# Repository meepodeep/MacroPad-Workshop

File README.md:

# MacroPad-Workshop
macro pad design for the CFMG workshop
# ASSEMBLY STEPS

1. bend the legs of the diodes and put them into the holes labeled d(x) on the back of the pcb (the side with the logo). make sure the black stripe on the diode is pointing to the square hole
2. solder them in from the side where they are sticking out
3. cut the legs off the diodes
4. click the switches into the plate with the pins facing up
5. solder the pin headers that were included with the microcontroller on the back side of the board (side with logo), the short side of the headers go through the pcb.
6. click the switches and plate onto the board and then solder the switches.
7. solder the microcontroller onto the pin headers one pin above the bottom, this is due to an error in the library i used.

# FLASHING STEPS

1. install qmk toolbox
2. install the cmfg_macropad_default.hex file from this repo
3. select it in qmk toolbox
4. select auto flash
5. connect the macropad to your computer and then short the reset and ground pins using some metal thing

# BOM

|Item        |Price|Quantity|Use              |Link                                                                                                                                                                                                                                                                                                                                                                                                                                                                                                                                                                                                                                                                                                                                                  |
|------------|-----|--------|-----------------|------------------------------------------------------------------------------------------------------------------------------------------------------------------------------------------------------------------------------------------------------------------------------------------------------------------------------------------------------------------------------------------------------------------------------------------------------------------------------------------------------------------------------------------------------------------------------------------------------------------------------------------------------------------------------------------------------------------------------------------------------|
|Switches    |5.81 |30pcs   |switches         |https://www.aliexpress.us/item/3256811859979458.html?spm=a2g0o.productlist.main.13.4eea570flhbmL7&algo_pvid=e65426b4-60f4-4fc9-9348-af8a4b587c54&algo_exp_id=e65426b4-60f4-4fc9-9348-af8a4b587c54-12&pdp_ext_f=%7B%22order%22%3A%2220%22%2C%22eval%22%3A%221%22%2C%22fromPage%22%3A%22search%22%7D&pdp_npi=6%40dis%21USD%2112.27%215.77%21%21%2182.80%2138.92%21%40210318a717799006729027642ea09d%2112000057360279622%21sea%21US%214381910819%21X%211%210%21n_tag%3A-29919%3Bd%3A747bdf24%3Bm03_new_user%3A-29895&curPageLogUid=bT9cObGFOkPD&utparam-url=scene%3Asearch%7Cquery_from%3A%7Cx_object_id%3A1005012046294210%7C_p_origin_prod%3A                                                                                                          |
|Pro micro   |4.38 |1       |runs the macropad|https://www.aliexpress.us/item/2251801390587459.html?spm=a2g0o.productlist.main.3.48bf6cd9PQeXzG&algo_pvid=fa6176a7-c4be-416b-9716-300483b20f90&algo_exp_id=fa6176a7-c4be-416b-9716-300483b20f90-2&pdp_ext_f=%7B%22order%22%3A%225295%22%2C%22eval%22%3A%221%22%2C%22fromPage%22%3A%22search%22%7D&pdp_npi=6%40dis%21USD%214.31%214.31%21%21%214.31%214.31%21%402101e2b217799006250502727eef1b%2112000030837890690%21sea%21US%214381910819%21X%211%210%21n_tag%3A-29919%3Bd%3A747bdf24%3Bm03_new_user%3A-29895&curPageLogUid=kLt6ooCUgbaQ&utparam-url=scene%3Asearch%7Cquery_from%3A%7Cx_object_id%3A1576902211%7C_p_origin_prod%3A                                                                                                                   |
|1N4148 Diode|2.68 |1       |is diode         |https://www.aliexpress.us/item/3256804886900665.html?spm=a2g0o.productlist.main.8.31e1648dN5UmVI&aem_p4p_detail=202605270952121212322309854570000188418&algo_pvid=a378f521-9b65-44cc-8d89-a025a8239f06&algo_exp_id=a378f521-9b65-44cc-8d89-a025a8239f06-7&pdp_ext_f=%7B%22order%22%3A%2290%22%2C%22eval%22%3A%221%22%2C%22fromPage%22%3A%22search%22%7D&pdp_npi=6%40dis%21USD%212.68%212.68%21%21%212.68%212.68%21%40210328d417799007320938248e1cda%2112000031530566687%21sea%21US%214381910819%21X%211%210%21n_tag%3A-29919%3Bd%3A747bdf24%3Bm03_new_user%3A-29895&curPageLogUid=XsiQyzmtc2jb&utparam-url=scene%3Asearch%7Cquery_from%3A%7Cx_object_id%3A1005005073215417%7C_p_origin_prod%3A&search_p4p_id=202605270952121212322309854570000188418_2|
|Keycaps     |4.07 |1       |is keycap        |https://www.aliexpress.us/item/3256808845306164.html?spm=a2g0o.productlist.main.3.5b1b5170kbpBCq&algo_pvid=a0e70af7-736c-44be-90c3-9ff2f53e2aa7&algo_exp_id=a0e70af7-736c-44be-90c3-9ff2f53e2aa7-2&pdp_ext_f=%7B%22order%22%3A%22173%22%2C%22eval%22%3A%221%22%2C%22fromPage%22%3A%22search%22%7D&pdp_npi=6%40dis%21USD%214.07%214.07%21%21%214.07%214.07%21%402101e80f17799008263841887effb5%2112000047649050621%21sea%21US%214381910819%21X%211%210%21n_tag%3A-29919%3Bd%3A747bdf24%3Bm03_new_user%3A-29895&curPageLogUid=K3evXPx26JyJ&utparam-url=scene%3Asearch%7Cquery_from%3A%7Cx_object_id%3A1005009031620916%7C_p_origin_prod%3A                                                                                                              |

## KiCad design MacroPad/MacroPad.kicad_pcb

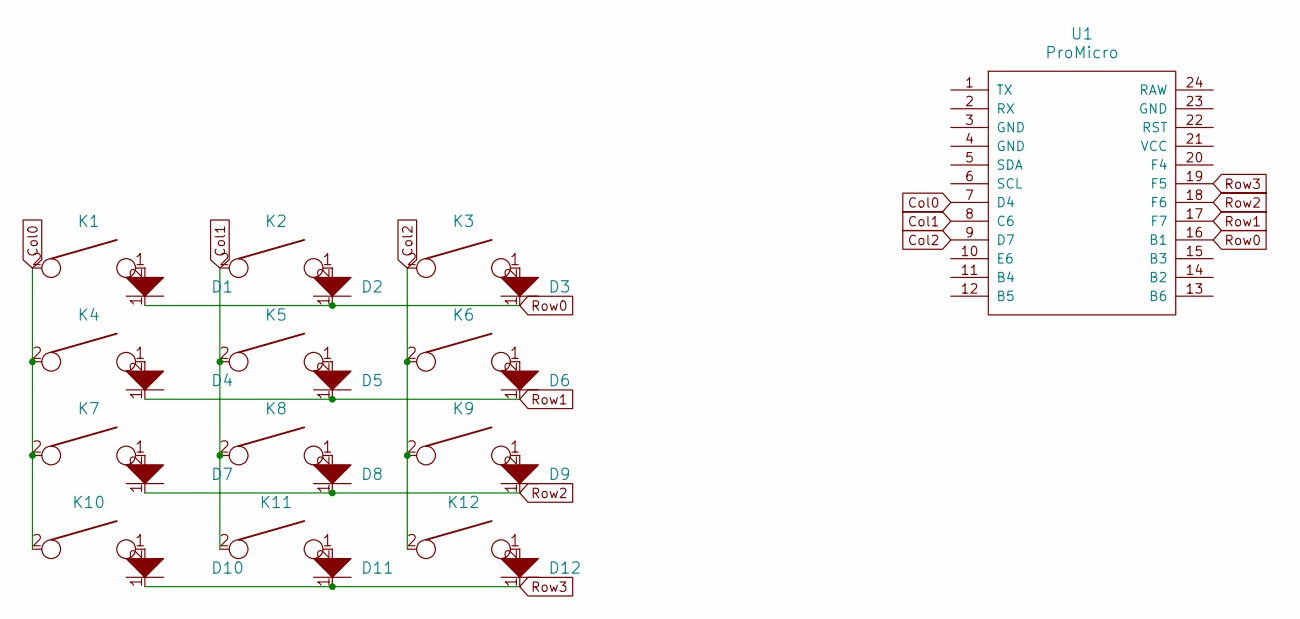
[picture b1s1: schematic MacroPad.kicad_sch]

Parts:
D1, D2, D3, D4, D5, D6, D7, D8, D9, D10, D11, D12: D; D_SOD123_axial
K1, K2, K3, K4, K5, K6, K7, K8, K9, K10, K11, K12: KEYSW; Mx_Alps_100
U1: ProMicro; Pro_Micro

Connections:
Col0: K1.2, K4.2, K7.2, K10.2, U1.7 (D4)
Col1: K2.2, K5.2, K8.2, K11.2, U1.8 (C6)
Col2: K3.2, K6.2, K9.2, K12.2, U1.9 (D7)
unnamed: D1.2, K1.1
unnamed: D2.2, K2.1
unnamed: D3.2, K3.1
unnamed: D4.2, K4.1
unnamed: D5.2, K5.1
unnamed: D6.2, K6.1
unnamed: D7.2, K7.1
unnamed: D8.2, K8.1
unnamed: D9.2, K9.1
unnamed: D10.2, K10.1
unnamed: D11.2, K11.1
unnamed: D12.2, K12.1
Row0: D1.1, D2.1, D3.1, U1.16 (B1)
Row1: D4.1, D5.1, D6.1, U1.17 (F7)
Row2: D7.1, D8.1, D9.1, U1.18 (F6)
Row3: D10.1, D11.1, D12.1, U1.19 (F5)

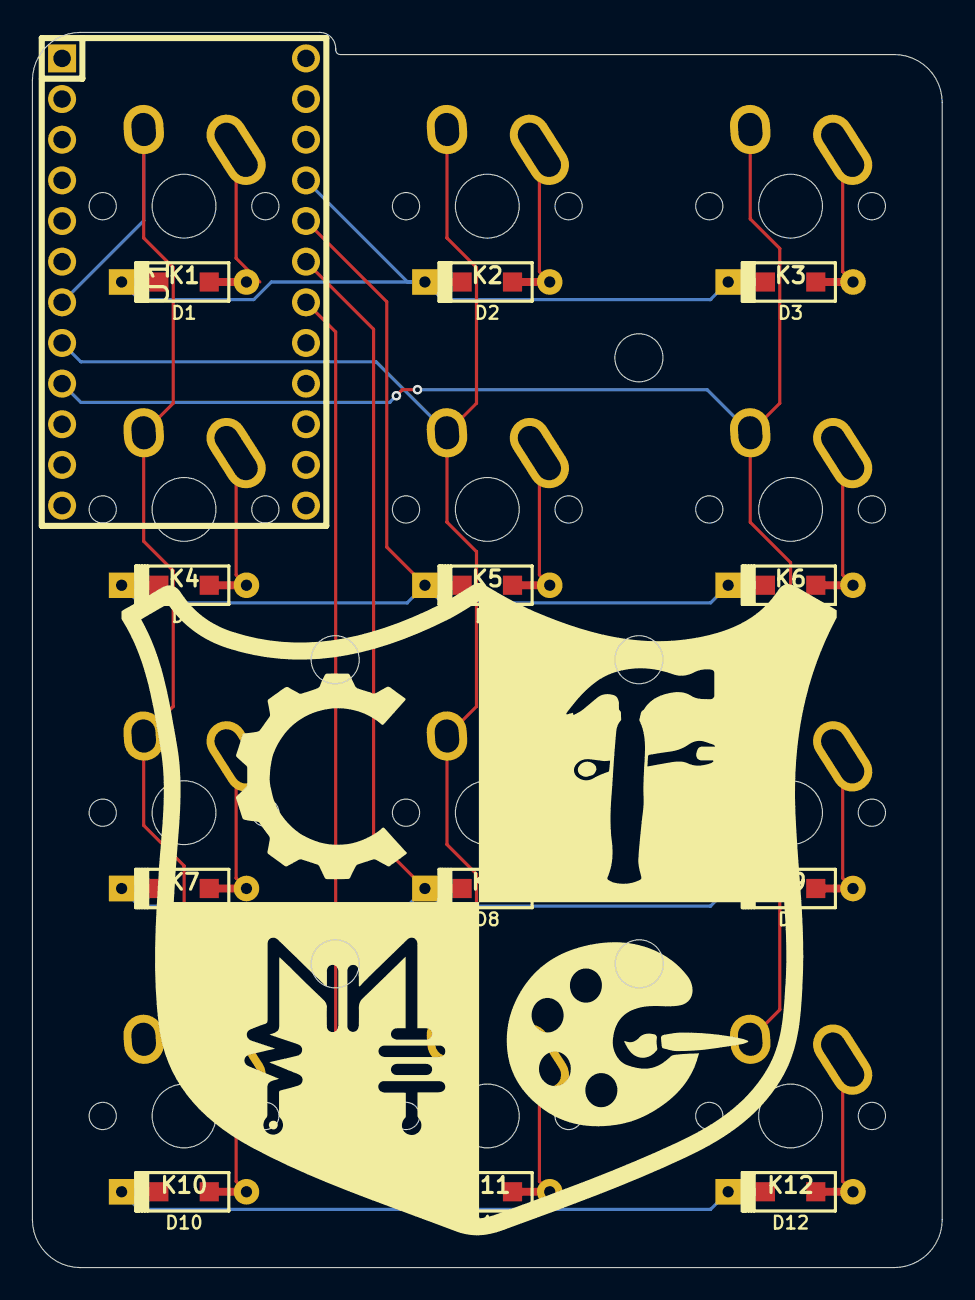
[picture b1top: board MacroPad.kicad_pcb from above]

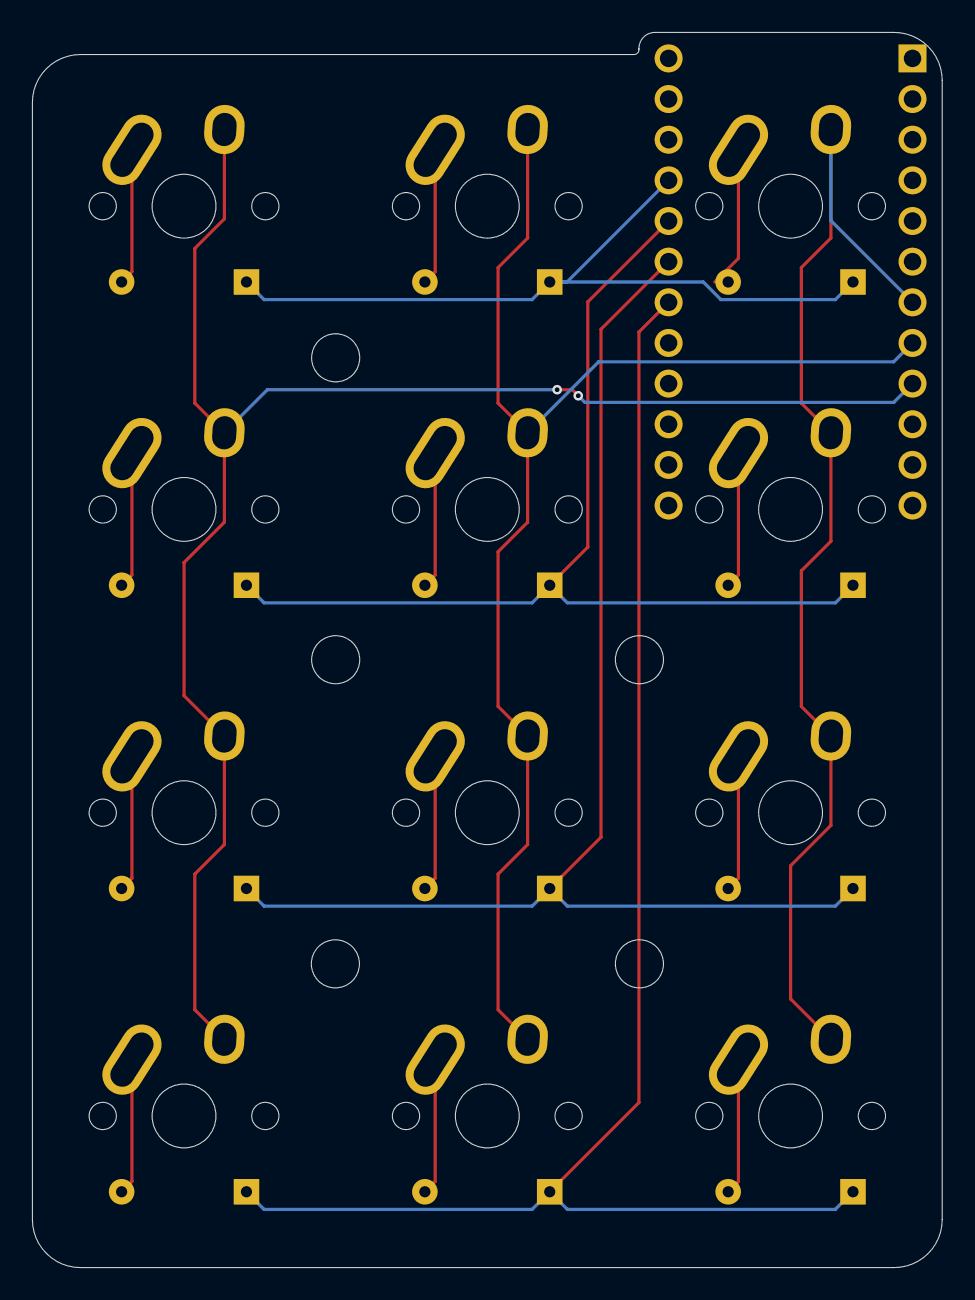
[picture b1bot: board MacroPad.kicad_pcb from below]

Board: 2 copper layers, 56.8 x 77.2 mm, 25 parts (12 on the bottom side), 19 nets.

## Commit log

2026-02-28 made pcb
